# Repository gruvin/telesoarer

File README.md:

# TeleSoarer
## A remote control, Lost Model Alarm &amp; Variometer, for Slope Soarers / Sailplanes.

#### UPDATED: 2016-12-22

This here is my existing [lost model alarm](https://github.com/gruvin/lostmodel), upgraded to include high resolution (10cm -- MS5611 chip sensor) analog vario output. The latter is intended for use with Fr-Sky telemetry on a Taranis radio. 

### But what _is_ it?
It gets used for RC model aircraft, "slope soaring". That is, flying about fighting gravity in breezy updrafts, without any intrinsic means of propulsion. So much fun! Sometimes, we goof up or get tossed asunder by vicious rotor (crazy wind!) and cannot find our model. That's where having an audible beacon comes in real handy. Without it, one can be literally one meter away from the aircraft, hiding in long grass just, "exactly where we saw it go in, right?!" ... and simply not be able to see the thing. So, now you know.

The vario — altitude change detector/signal — is in this case, really just for fun. I imagine it to be of _far_ more practical use in a _thermal_ sailplane. But, I'm doing it for the slope anyway.

### Firmware — STM32 MCU
TeleSoarer gets an upgrade from 8bit ATmega88P MCU to a 32bit ARM based, STM32F103CBT. I first discovered this excellent little MCU on a LeafLabs Maple-mini. But that's a whole other story.

Whilst there are a few great efforts to get Arduino style programming of 32bit chips working, I found them all to be a bit too flakey at the moment. So for this project, I used ST's new(ish) `STM32CubeMX` software, which makes short work of writing start-up C code for setting up a STM32 with my chosen peripherals and configuration. It's all done in pure C language, not C++. Whatever. I found the whole experience simply excellent for quick-out-of-thje-gate STM32 development. Well done ST!

### It's LOUD
The alarm itself is LOUD -- because that was the original purpose behind making my own. The MCU outputs a ~2.8KHz square wave at around 15% duty cycle. This is fed to an autotransformer, before arriving at a mechanical cavity resonated, quartz wafer thingy (piezo) . All this produces a head-splittingly LOUD tone — indoors at least. Why? Well in practice, models get lost in long grass, on windy, noisy slopes. The paltry beepers available off the shelf are all but useless in these conditions.

### OLED Display
This new version also includes a 0.91" OLED display, just for kicks really. It gives the whole thing a more friendly user interface for changing settings, if nothing else. 

### Prototype
The complete system has been tested on a breadboard ...

Amazing how big a prototype circuit can be, before getting onto its final PCB.

### PCB
As of this writing, the PCB has been designed, but not yet ordered. Here's a KiCAD rendering of the PCB ... because they're just so darn cute ...

The piezo section can be chopped off and remote mounted. An OLED display goes on the back.

### The Why
The point of this project was to obtain a nice small footprint, while doing away with all the clunky wires needed for off-the-shelf Fr-Sky telemetry modules (for example). This thing is tiny and will be a welcomed space saver.

I have no idea if anyone else will ever be interested. Drop me a line if that's you. I'd love to know! ;-)

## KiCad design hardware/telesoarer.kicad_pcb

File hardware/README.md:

# Hardware

## Designed in KiCAD v4

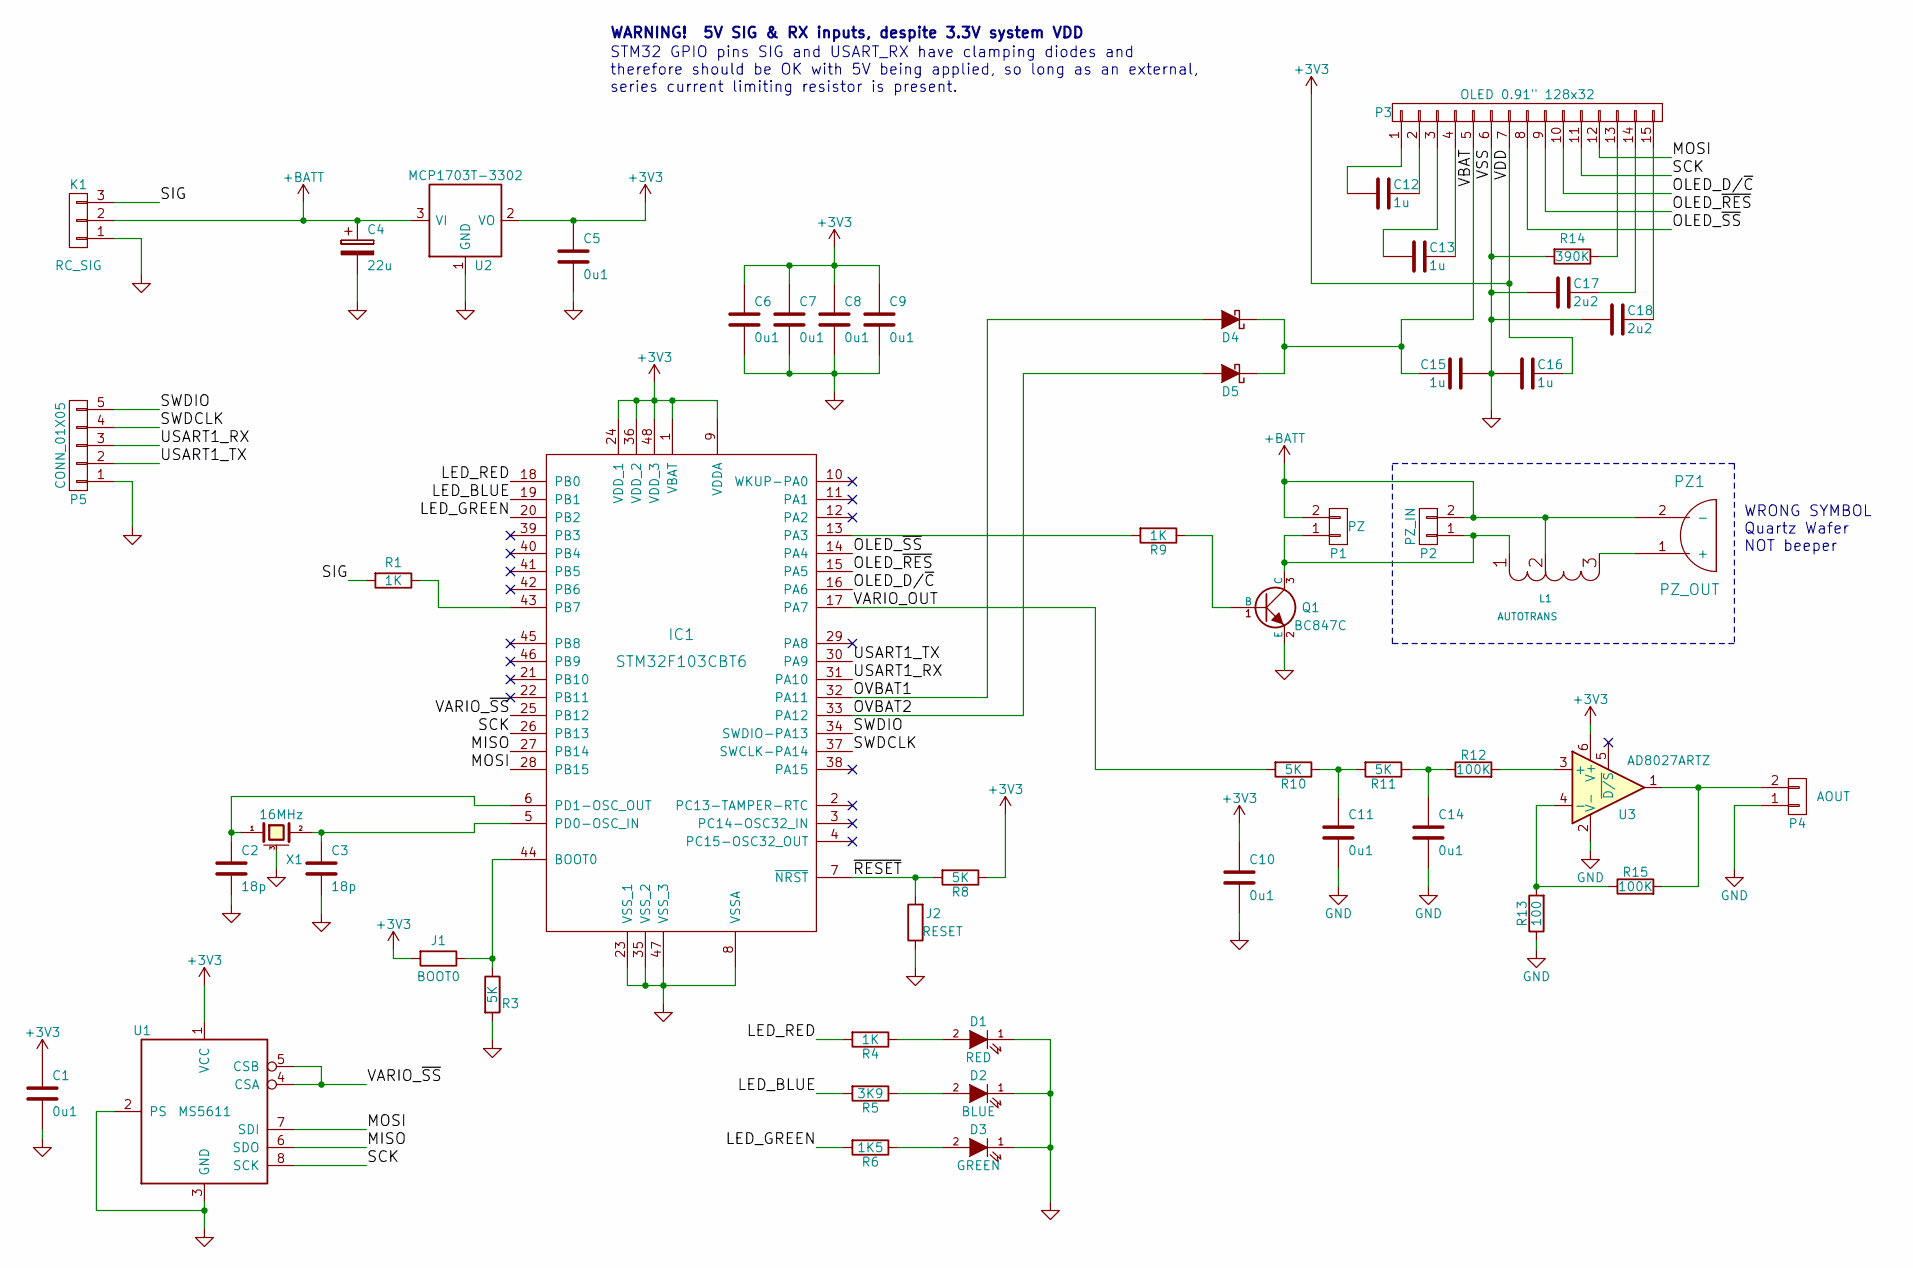
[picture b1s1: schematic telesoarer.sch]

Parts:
C1, C5, C6, C7, C8, C9, C10, C11, C14: 0u1; C_0402
C2, C3: 18p; C_0402
C4: 22u; TantalC_SizeS_EIA-3216
C12, C13, C15, C16: 1u; C_0402
C17, C18: 2u2; C_0402
D1: RED; LED_0603
D2: BLUE; LED_0603
D3: GREEN; LED_0603
D4, D5: D_Schottky; SOD-523
IC1: STM32F103CBT6; LQFP-48_7x7mm_Pitch0.5mm
J1: BOOT0; BR_O_0603
J2: RESET; BR_O_0603
K1: RC_SIG; Pin_Header_Angled_1x03
L1: AUTOTRANS; TRI-3
P1: PZ; JST_SH_SM02B-SRSS-TB_02x1.00mm_Angled
P2: PZ_IN; JST_SH_SM02B-SRSS-TB_02x1.00mm_Angled
P3: OLED 0.91\" 128x32; ZIF_FPC15
P4: AOUT; Pin_Header_Angled_1x02
P5: CONN_01X05; JST_SH_SM05B-SRSS-TB_05x1.00mm_Angled
PZ1: PZ_OUT; PIN_ARRAY_2X1
Q1: BC847C; SOT23-BCE
R1, R4, R9: 1K; R_0402
R3, R8, R10, R11: 5K; R_0402
R5: 3K9; R_0402
R6: 1K5; R_0402
R12, R15: 100K; R_0402
R13: 100; R_0402
R14: 390K; R_0402
U1: MS5611; MS5611_8_3mmx5mm_SMD
U2: MCP1703T-3302; SOT-23A
U3: AD8027ARTZ; SOT-23-6
X1: 16MHz; Crystal_SMD_2520_4Pads

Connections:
+3V3: C1.1, C5.1, C6.1, C7.1, C8.1, C9.1, C10.1, C16.1, IC1.1 (VBAT), IC1.9 (VDDA), IC1.24 (VDD_1), IC1.36 (VDD_2), IC1.48 (VDD_3), J1.2, P3.7, R8.1, U1.1 (VCC), U2.2 (VO), U3.6 (V+)
+BATT: C4.1, K1.2, L1.2, P1.2, P2.2, PZ1.2 (-), U2.3 (VI)
/LED_BLUE: IC1.19 (PB1), R5.2
/LED_GREEN: IC1.20 (PB2), R6.2
/LED_RED: IC1.18 (PB0), R4.2
/MISO: IC1.27 (PB14), U1.6 (SDO)
/MOSI: IC1.28 (PB15), P3.12, U1.7 (SDI)
/OLED_D/~C: IC1.16 (PA6), P3.10
/OLED_~RES: IC1.15 (PA5), P3.9
/OLED_~SS: IC1.14 (PA4), P3.8
/OVBAT1: D4.2 (A), IC1.32 (PA11)
/OVBAT2: D5.2 (A), IC1.33 (PA12)
/SCK: IC1.26 (PB13), P3.11, U1.8 (SCK)
/SIG: K1.3, R1.2
/SWDCLK: IC1.37 (SWCLK-PA14), P5.4
/SWDIO: IC1.34 (SWDIO-PA13), P5.5
/USART1_RX: IC1.31 (PA10), P5.3
/USART1_TX: IC1.30 (PA9), P5.2
/VARIO_OUT: IC1.17 (PA7), R10.2
/VARIO_~SS: IC1.25 (PB12), U1.4 (CSA), U1.5 (CSB)
/VBAT: C15.2, D4.1 (K), D5.1 (K), P3.5
/~RESET: IC1.7 (~NRST), J2.2, R8.2
GND: C1.2, C2.2, C3.2, C4.2, C5.2, C6.2, C7.2, C8.2, C9.2, C10.2, C11.2, C14.2, C15.1, C16.2, C17.2, C18.2, D1.1 (K), D2.1 (K), D3.1 (K), IC1.8 (VSSA), IC1.23 (VSS_1), IC1.35 (VSS_2), IC1.47 (VSS_3), J2.1, K1.1, P3.6, P4.1, P5.1, Q1.2 (E), R3.2, R13.1, R14.2, U1.2 (PS), U1.3 (GND), U2.1 (GND), U3.2 (V-), X1.3 (case)
unnamed: C2.1, IC1.6 (PD1-OSC_OUT), X1.1
unnamed: C3.1, IC1.5 (PD0-OSC_IN), X1.2
unnamed: C11.1, R10.1, R11.2
unnamed: C12.1, P3.2
unnamed: C12.2, P3.1
unnamed: C13.1, P3.4
unnamed: C13.2, P3.3
unnamed: C14.1, R11.1, R12.1
unnamed: C17.1, P3.14
unnamed: C18.1, P3.15
unnamed: D1.2 (A), R4.1
unnamed: D2.2 (A), R5.1
unnamed: D3.2 (A), R6.1
unnamed: IC1.13 (PA3), R9.2
unnamed: IC1.43 (PB7), R1.1
unnamed: IC1.44 (BOOT0), J1.1, R3.1
unnamed: L1.1, P1.1, P2.1, Q1.3 (C)
unnamed: L1.3, PZ1.1 (+)
unnamed: P3.13, R14.1
unnamed: P4.2, R15.2, U3.1
unnamed: Q1.1 (B), R9.1
unnamed: R12.2, U3.3 (+)
unnamed: R13.2, R15.1, U3.4 (-)

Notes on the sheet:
WRONG SYMBOL Quartz Wafer NOT beeper
STM32 GPIO pins SIG and USART_RX have clamping diodes and therefore should be OK with 5V being applied, so long as an external, series current limiting resistor is present.
WARNING! 5V SIG & RX inputs, despite 3.3V system VDD

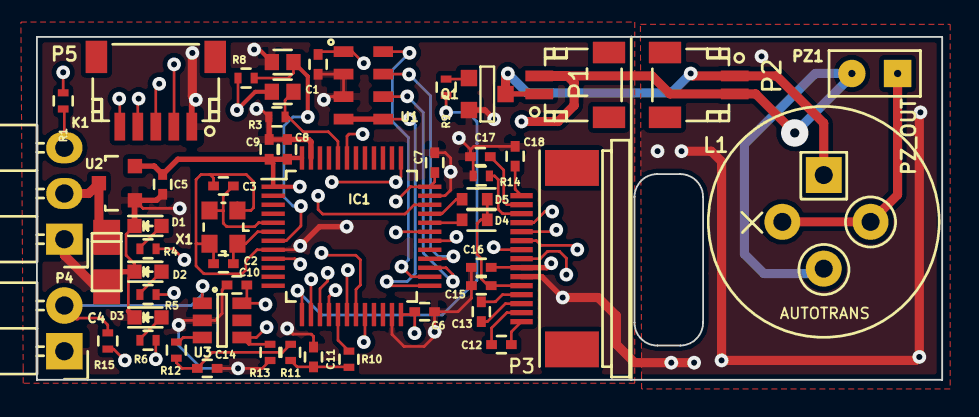
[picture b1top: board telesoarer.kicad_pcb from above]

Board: 4 copper layers, 50.3 x 19.1 mm, 52 parts (0 on the bottom side), 46 nets.

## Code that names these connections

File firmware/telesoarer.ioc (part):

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Mcu.Name=STM32F103C(8-B)Tx
Mcu.Package=LQFP48
Mcu.UserName=STM32F103CBTx
PA10.Mode=Asynchronous
PA10.Signal=USART1_RX
PA11.GPIOParameters=GPIO_Label
PA11.GPIO_Label=OVBAT1
PA11.Signal=GPIO_Output
PA12.GPIOParameters=GPIO_Label
PA12.GPIO_Label=OVBAT2
PA12.Signal=GPIO_Output
PA13.Mode=Serial_Wire
PA13.Signal=SYS_JTMS-SWDIO
PA14.Mode=Serial_Wire
PA14.Signal=SYS_JTCK-SWCLK
PA3.GPIOParameters=GPIO_ModeDefaultPP,GPIO_Label
PA3.GPIO_Label=PIEZO
PA3.GPIO_ModeDefaultPP=GPIO_MODE_AF_PP
PA3.Signal=S_TIM2_CH4
PA4.GPIOParameters=GPIO_Label
PA4.GPIO_Label=OLED_SS
PA4.Signal=GPIO_Output
PA5.GPIOParameters=GPIO_Speed,PinState,GPIO_Label
PA5.GPIO_Label=OLED_RES
PA5.GPIO_Speed=GPIO_SPEED_FREQ_MEDIUM
PA5.PinState=GPIO_PIN_SET
PA5.Signal=GPIO_Output
PA6.GPIOParameters=GPIO_Speed,PinState,GPIO_Label
PA6.GPIO_Label=OLED_DC
PA6.GPIO_Speed=GPIO_SPEED_FREQ_MEDIUM
PA6.PinState=GPIO_PIN_SET
PA6.Signal=GPIO_Output
PA7.GPIOParameters=GPIO_Label
PA7.GPIO_Label=VARIO_OUT
PA7.Signal=S_TIM3_CH2
PA9.Mode=Asynchronous
PA9.Signal=USART1_TX
PB0.GPIOParameters=GPIO_Label
PB0.GPIO_Label=LED_RED
PB0.Signal=GPIO_Output
PB1.GPIOParameters=GPIO_Label
PB1.GPIO_Label=LED_BLUE
PB1.Signal=GPIO_Output
PB12.GPIOParameters=GPIO_Speed,PinState,GPIO_Label
PB12.GPIO_Label=VARIO_SS
PB12.GPIO_Speed=GPIO_SPEED_FREQ_HIGH
PB12.PinState=GPIO_PIN_SET
PB12.Signal=GPIO_Output
PB13.GPIOParameters=GPIO_Speed
PB13.GPIO_Speed=GPIO_SPEED_FREQ_HIGH
PB13.Mode=Full_Duplex_Master
PB13.Signal=SPI2_SCK
PB14.Mode=Full_Duplex_Master
PB14.Signal=SPI2_MISO
PB15.GPIOParameters=GPIO_Speed
PB15.GPIO_Speed=GPIO_SPEED_FREQ_HIGH
PB15.Mode=Full_Duplex_Master
PB15.Signal=SPI2_MOSI
PB2.GPIOParameters=GPIO_Label
PB2.GPIO_Label=LED_GREEN
PB2.Signal=GPIO_Output
PB7.GPIOParameters=GPIO_Label
PB7.GPIO_Label=SIG
PB7.Signal=S_TIM4_CH2
PD0-OSC_IN.Mode=HSE-External-Oscillator
PD0-OSC_IN.Signal=RCC_OSC_IN
PD1-OSC_OUT.Mode=HSE-External-Oscillator
PD1-OSC_OUT.Signal=RCC_OSC_OUT
RCC.SYSCLKFreq_VALUE=72000000
RCC.SYSCLKSource=RCC_SYSCLKSOURCE_PLLCLK
board=telesoarer

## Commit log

2016-10-31 Added main README
2016-11-01 Fixed gitignore issue that was filtering out KiCAD component libraries from global_gitignore on my system. Add local git ignores for convenience of newcomers, I hope.
2016-11-01 Fixed gitignore for KiCAD component libraries (*.lib)
2016-11-01 PCB tweaks
2016-11-01 image update
2016-11-01 README.md update
2016-11-02 Reduced PCB size.
2016-11-03 Moved high voltage piezo output away from delicate analog output. Other minor changes.
2016-11-05 Need 16MHz xtal for Arduino bootloader serial to work -- clock too inaccurate at 8MHz RC. Added OLED display and the somewhat important 3.3V regulator I completely forgot about before!
2016-11-06 Added AD8027 op-amp datasheet
2016-11-07 Added DAC filter from partsim.com simulation. Employs a two stage RC low pass filter, followed by an Analog Device AD8027 rail-to-rail op-amp (SOT-23 6pin 3x3mm package)
2016-11-07 Minor DAC filter scmetaic tweaks
2016-11-07 Added partsim.com DAC fitler response plot
2016-11-07 Updated partsim.com DAC fitler response plot
2016-11-07 Switching to NXP ARM chip. Added reference files.
2016-11-11 Ripping things apart for the change to STM32 chipa
2016-11-23 Schematic updates for change to STM32F103 MCU
2016-11-24 STM32CubeMX Project ported into telesoarer.
2016-11-24 Add untracked files. Updated .gitignore
2016-11-24 Added new kicad-share submodule. Uses existing KiCAD preferences path, hardware/share
2016-11-24 Completed first draft of STM32 based schematic. (Added Vario output LPF.)
2016-11-25 Work on STM32 / OLED PCB design begins
2016-11-25 KiCAD share update
2016-11-25 PCB progress check-in
2016-11-26 PCB work continues
2016-11-26 sub module won't sync
2016-11-26 More PCB work
2016-11-26 If I don't quit now, I may find myself divorced. To the morrow, then!
2016-11-27 MILESTONE: PCB Routing Completed (FINAL DRAFT 1)
2016-11-27 Oscillator Keep-out and GND shield changes
2016-11-28 PCB updates
2016-11-28 PCB updates -- mostly JST/FPC socket 3D packages.
2016-12-20 Added some PCB dimensions
2016-12-20 STM32 flash convenience script
2016-12-22 Added breadboard prototype photo, for posterity.
